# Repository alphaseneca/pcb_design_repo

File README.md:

# pcb_design_repo

A repository for storing and documenting the pcb design files.

### ST-RF

### STM32F4_Breakout

### STM32F4_Breakout_REV2

### STM32WB-Bluetooth_Hardware_Design

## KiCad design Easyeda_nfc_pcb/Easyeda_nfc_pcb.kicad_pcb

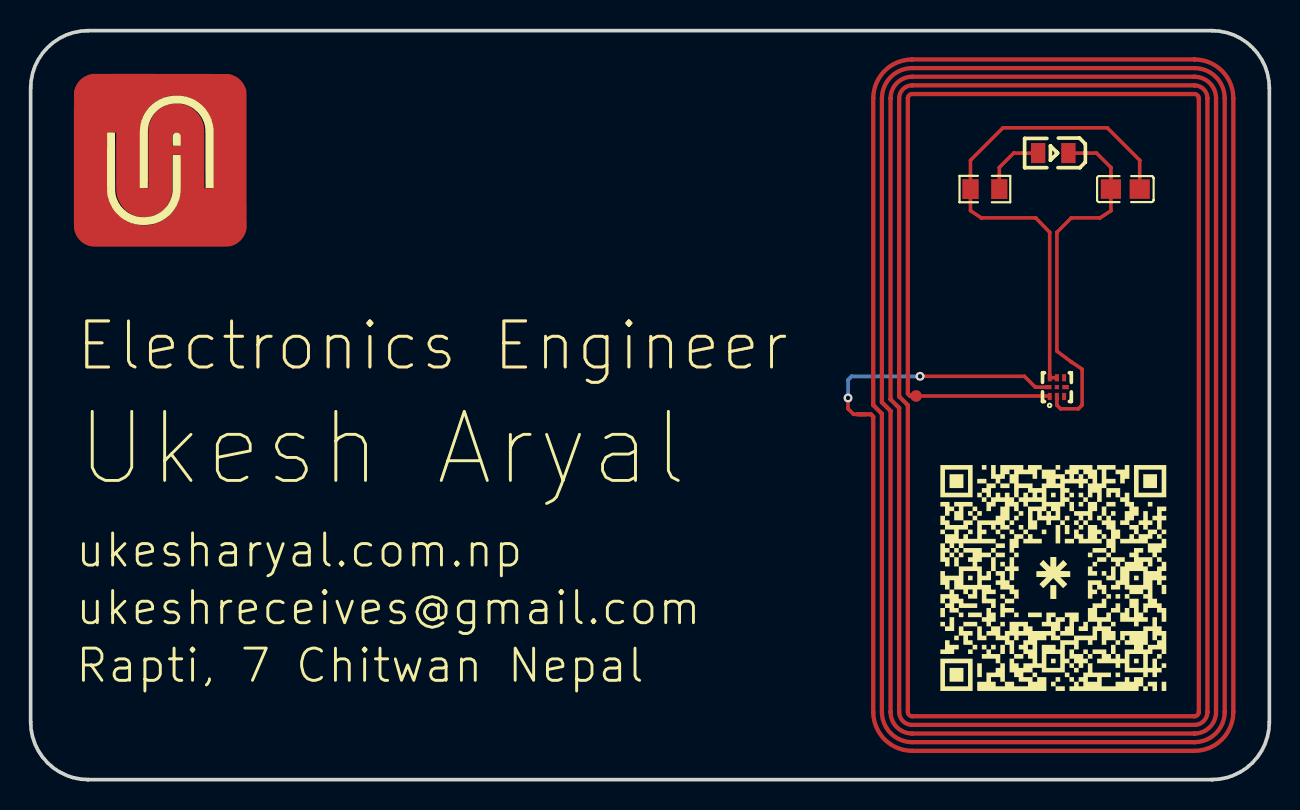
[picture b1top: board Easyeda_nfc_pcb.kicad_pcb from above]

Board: 2 copper layers, 86.0 x 52.0 mm, 5 parts (0 on the bottom side), 5 nets.

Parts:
1: 25X48MM_NFC_ANTENNA
C2: 220nF; C0805
LED1: 17-21SUYC/TR8; LED0805-R-RD
R1: 47Ω; R0805
U1: NT3H2111W0FHKH; XQFN-8_L1.6-W1.6-P0.50-BL

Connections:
LED1_1: LED1.1, R1.1
U1_1: 1.P$2, U1.1
U1_2: C2.1, LED1.2, U1.2
U1_7: C2.2, R1.2, U1.6, U1.7
U1_8: 1.P$1, U1.8

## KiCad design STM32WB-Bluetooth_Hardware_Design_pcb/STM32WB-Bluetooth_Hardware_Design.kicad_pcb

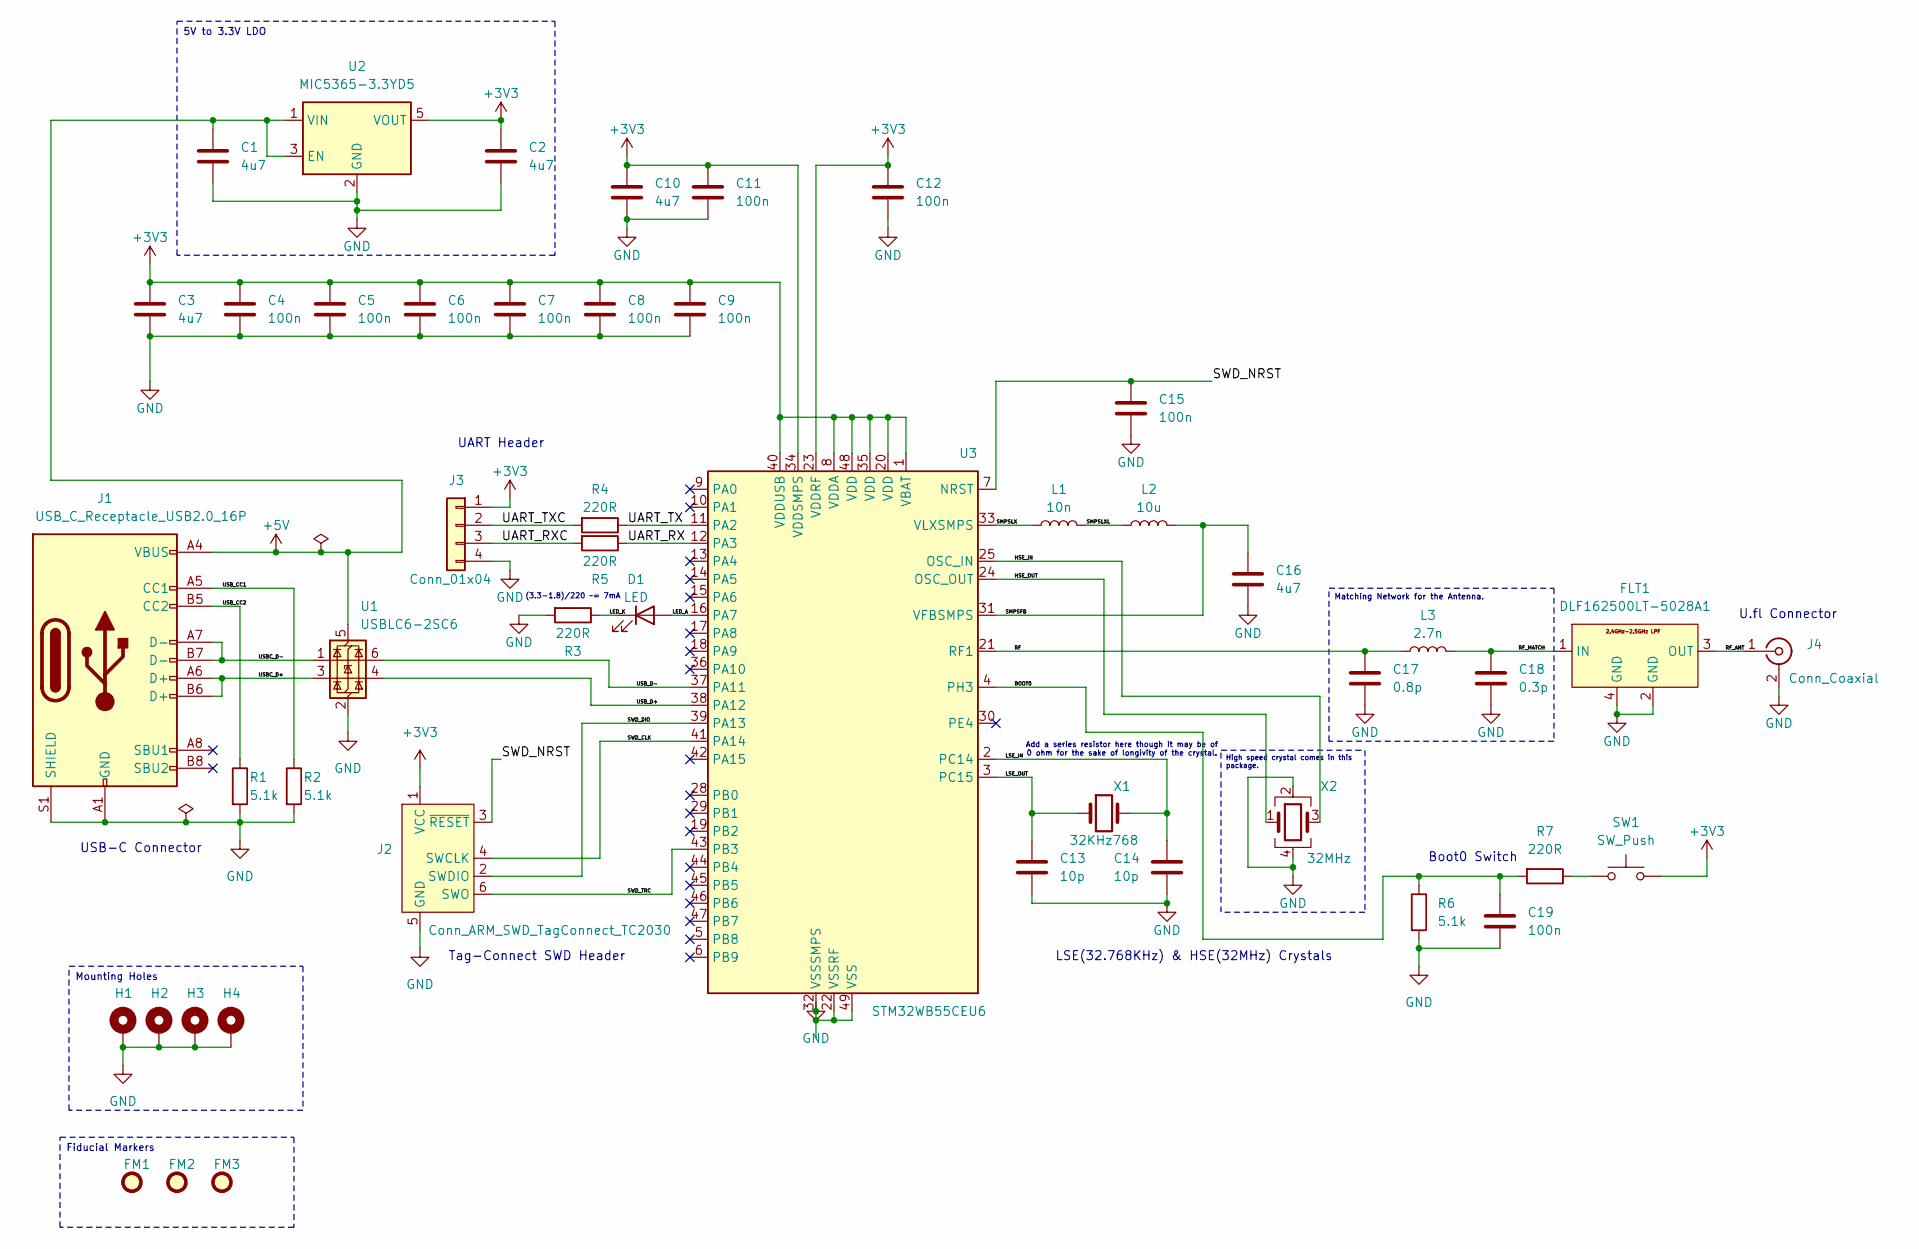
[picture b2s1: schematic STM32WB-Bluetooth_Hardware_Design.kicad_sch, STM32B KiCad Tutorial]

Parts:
C1, C2, C3, C10, C16: 4u7; C_0603_1608Metric
C4, C5, C6, C7, C8, C9, C11, C12, C15, C19: 100n; C_0402_1005Metric
C13, C14: 10p; C_0402_1005Metric
C17: 0.8p; C_0402_1005Metric
C18: 0.3p; C_0402_1005Metric
D1: LED; LED_0402_1005Metric
FLT1: DLF162500LT-5028A1
FM1, FM2, FM3: Fiducial; Fiducial_0.5mm_Mask1mm
H1, H2, H3, H4: MountingHole_Pad; MountingHole_2.2mm_M2_Pad_Via
J1: USB_C_Receptacle_USB2.0_16P; USB_C_Receptacle_GCT_USB4105-xx-A_16P_TopMnt_Horizontal
J2: Conn_ARM_SWD_TagConnect_TC2030; Tag-Connect_TC2030-IDC-FP_2x03_P1.27mm_Vertical
J3: Conn_01x04; Molex_PicoBlade_53048-0410_1x04_P1.25mm_Horizontal
J4: Conn_Coaxial; U.FL_Hirose_U.FL-R-SMT-1_Vertical
L1: 10n; L_0402_1005Metric
L2: 10u; L_0805_2012Metric
L3: 2.7n; L_0402_1005Metric
R1, R2, R6: 5.1k; R_0402_1005Metric
R3, R4, R5, R7: 220R; R_0402_1005Metric
SW1: SW_Push; SW_SPST_B3U-1000P
U1: USBLC6-2SC6; SOT-23-6
U2: MIC5365-3.3YD5; SOT-23-5
U3: STM32WB55CEU6; QFN-48-1EP_7x7mm_P0.5mm_EP5.6x5.6mm
X1: 32KHz768; Crystal_SMD_2012-2Pin_2.0x1.2mm
X2: 32MHz; Crystal_SMD_2016-4Pin_2.0x1.6mm

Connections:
+3V3: C2.1, C3.1, C4.1, C5.1, C6.1, C7.1, C8.1, C9.1, C10.1, C11.1, C12.1, J2.1 (VCC), J3.1, SW1.2, U2.5 (VOUT), U3.1 (VBAT), U3.8 (VDDA), U3.20 (VDD), U3.23 (VDDRF), U3.34 (VDDSMPS), U3.35 (VDD), U3.40 (VDDUSB), U3.48 (VDD)
+5V: C1.1, J1.A4 (VBUS), J1.A9 (VBUS), J1.B4 (VBUS), J1.B9 (VBUS), U1.5 (VBUS), U2.1 (VIN), U2.3 (EN)
/BOOT0: C19.1, R6.1, R7.2, U3.4 (PH3)
/HSE_IN: U3.25 (OSC_IN), X2.3
/HSE_OUT: U3.24 (OSC_OUT), X2.1
/LED_A: D1.2 (A), U3.16 (PA7)
/LED_K: D1.1 (K), R3.1
/LSE_IN: C14.1, U3.2 (PC14), X1.2
/LSE_OUT: C13.1, U3.3 (PC15), X1.1
/RF: C17.1, L3.1, U3.21 (RF1)
/RF_ANT: FLT1.3 (OUT), J4.1 (In)
/RF_MATCH: C18.1, FLT1.1 (IN), L3.2
/SMPSFB: C16.1, L2.2, U3.31 (VFBSMPS)
/SMPSLX: L1.1, U3.33 (VLXSMPS)
/SMPSLXL: L1.2, L2.1
/SWD_CLK: J2.4 (SWCLK), U3.41 (PA14)
/SWD_DIO: J2.2 (SWDIO), U3.39 (PA13)
/SWD_NRST: C15.1, J2.3 (~RESET), U3.7 (NRST)
/SWD_TRC: J2.6 (SWO), U3.43 (PB3)
/UART_RX: R5.1, U3.12 (PA3)
/UART_RXC: J3.3, R5.2
/UART_TX: R4.1, U3.11 (PA2)
/UART_TXC: J3.2, R4.2
/USBC_D+: J1.A6 (D+), J1.B6 (D+), U1.3 (I/O2)
/USBC_D-: J1.A7 (D-), J1.B7 (D-), U1.1 (I/O1)
/USB_CC1: J1.A5 (CC1), R2.1
/USB_CC2: J1.B5 (CC2), R1.1
/USB_D+: U1.4 (I/O2), U3.38 (PA12)
/USB_D-: U1.6 (I/O1), U3.37 (PA11)
GND: C1.2, C2.2, C3.2, C4.2, C5.2, C6.2, C7.2, C8.2, C9.2, C10.2, C11.2, C12.2, C13.2, C14.2, C15.2, C16.2, C17.2, C18.2, C19.2, FLT1.2 (GND), FLT1.4 (GND), H1.1, H2.1, H3.1, H4.1, J1.A1 (GND), J1.A12 (GND), J1.B1 (GND), J1.B12 (GND), J1.S1 (SHIELD), J2.5 (GND), J3.4, J4.2 (Ext), R1.2, R2.2, R3.2, R6.2, U1.2 (GND), U2.2 (GND), U3.22 (VSSRF), U3.32 (VSSSMPS), U3.49 (VSS), X2.2, X2.4
unnamed: R7.1, SW1.1

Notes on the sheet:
Fiducial Markers
Mounting Holes
Matching Network for the Antenna.
5V to 3.3V LDO
High speed crystal comes in this package.
Add a series resistor here though it may be of 0 ohm for the sake of longivity of the crystal.
(3.3-1.8)/220 ~= 7mA
Tag-Connect SWD Header
USB-C Connector
LSE(32.768KHz) & HSE(32MHz) Crystals
U.fl Connector
Boot0 Switch
UART Header

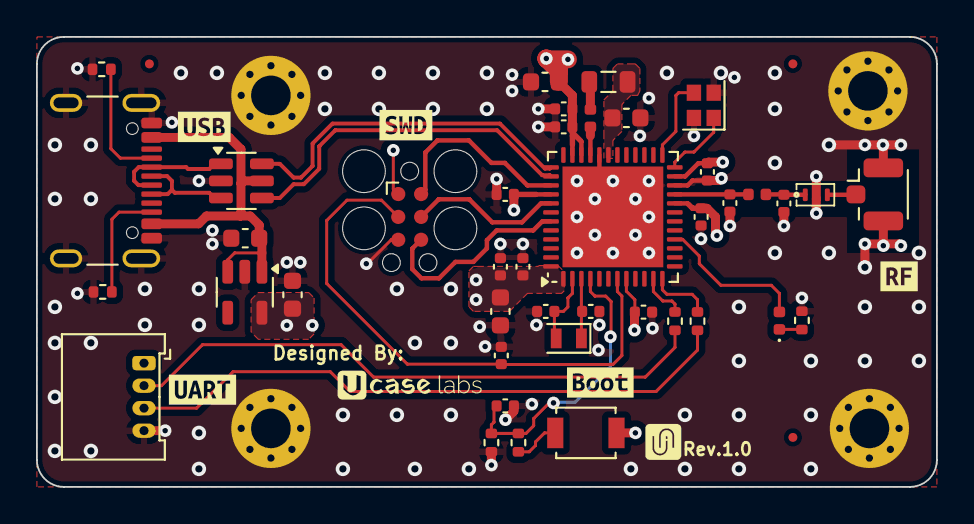
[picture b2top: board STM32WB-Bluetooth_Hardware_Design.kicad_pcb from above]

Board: 4 copper layers, 50.0 x 25.0 mm, 53 parts (0 on the bottom side), 31 nets.

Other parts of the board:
kibuzzard-663E8D7A: G***; kibuzzard-663E8D7A
kibuzzard-663E8D97: G***; kibuzzard-663E8D97
kibuzzard-663E8DAE: G***; kibuzzard-663E8DAE
kibuzzard-663E8DF2: G***; kibuzzard-663E8DF2
kibuzzard-663E8E0C: G***; kibuzzard-663E8E0C

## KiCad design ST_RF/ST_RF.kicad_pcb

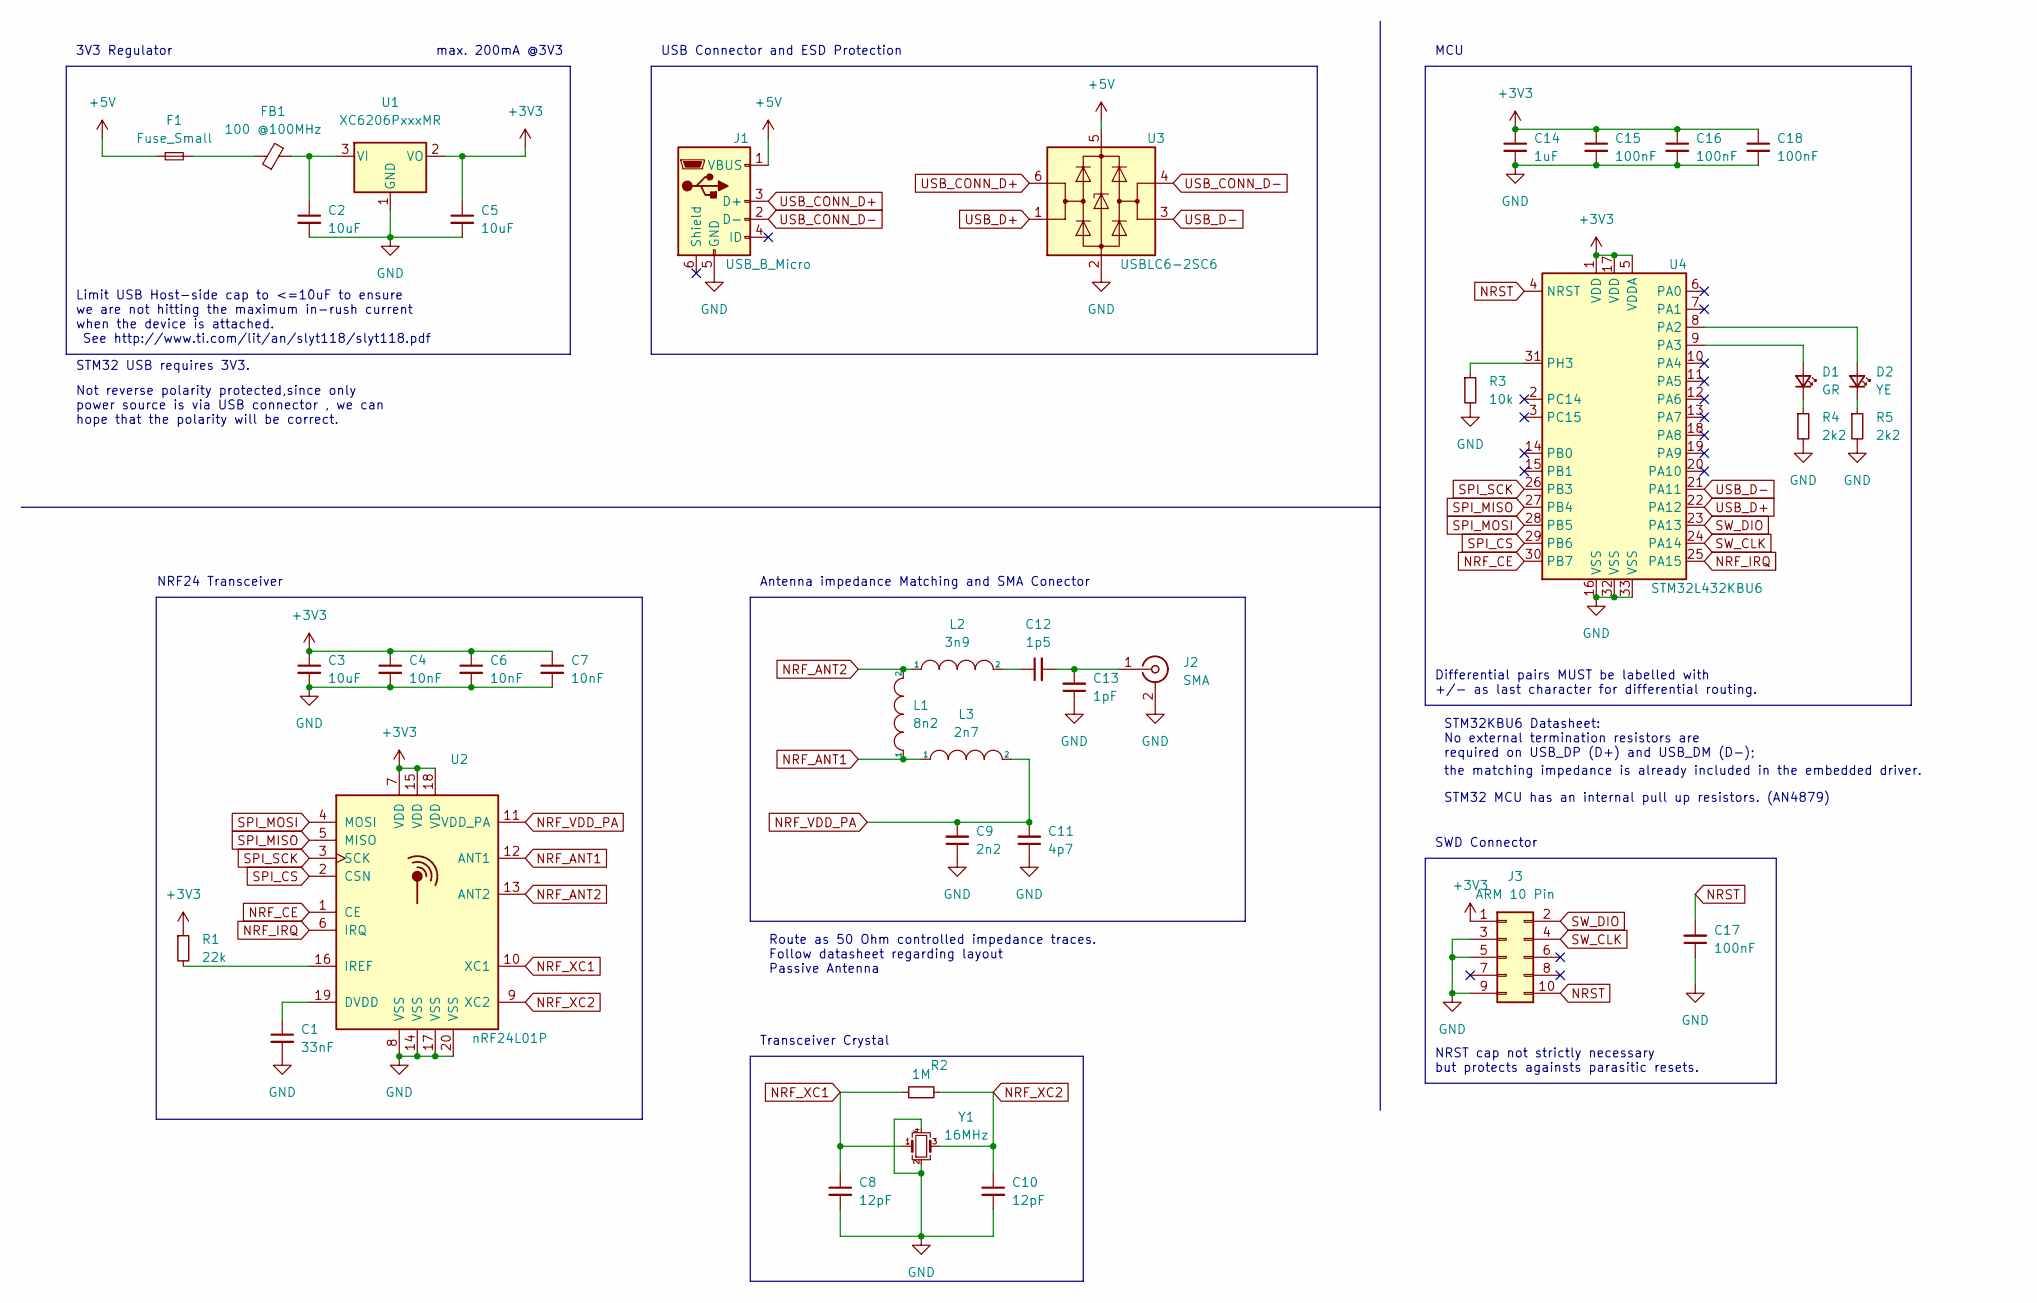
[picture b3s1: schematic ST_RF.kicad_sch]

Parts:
C1: 33nF; C_0402_1005Metric
C2, C3, C5: 10uF; C_0603_1608Metric
C4, C6, C7: 10nF; C_0402_1005Metric
C8, C10: 12pF; C_0402_1005Metric
C9: 2n2; C_0402_1005Metric
C11: 4p7; C_0402_1005Metric
C12: 1p5; C_0402_1005Metric
C13: 1pF; C_0402_1005Metric
C14: 1uF; C_0402_1005Metric
C15, C16, C17, C18: 100nF; C_0402_1005Metric
D1: GR; LED_0603_1608Metric
D2: YE; LED_0603_1608Metric
F1: Fuse_Small; Fuse_1206_3216Metric
FB1: 100 @100MHz; L_0805_2012Metric
J1: USB_B_Micro; USB_Micro-B_Molex-105017-0001
J2: SMA; SMA_Samtec_SMA-J-P-X-ST-EM1_EdgeMount
J3: ARM 10 Pin; PinHeader_2x05_P1.27mm_Vertical
L1: 8n2; L_0402_1005Metric
L2: 3n9; L_0402_1005Metric
L3: 2n7; L_0402_1005Metric
R1: 22k; R_0402_1005Metric
R2: 1M; R_0402_1005Metric
R3: 10k; R_0402_1005Metric
R4, R5: 2k2; R_0603_1608Metric
U1: XC6206PxxxMR; SOT-23
U2: nRF24L01P; QFN-20-1EP_4x4mm_P0.5mm_EP2.5x2.5mm
U3: USBLC6-2SC6; SOT-23-6
U4: STM32L432KBU6; QFN-32-1EP_5x5mm_P0.5mm_EP3.45x3.45mm
Y1: 16MHz; Crystal_SMD_3225-4Pin_3.2x2.5mm

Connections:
+3V3: C3.1, C4.1, C5.1, C6.1, C7.1, C14.1, C15.1, C16.1, C18.1, J3.1, R1.1, U1.2 (VO), U2.7 (VDD), U2.15 (VDD), U2.18 (VDD), U4.1 (VDD), U4.5 (VDDA), U4.17 (VDD)
+5V: F1.1, J1.1 (VBUS), U3.5 (VBUS)
GND: C1.2, C2.2, C3.2, C4.2, C5.2, C6.2, C7.2, C8.2, C9.1, C10.2, C11.1, C13.1, C14.2, C15.2, C16.2, C17.1, C18.2, J1.5 (GND), J2.2 (Ext), J3.3, J3.5, J3.9, R3.2, R4.2, R5.2, U1.1 (GND), U2.8 (VSS), U2.14 (VSS), U2.17 (VSS), U2.20 (VSS), U3.2 (GND), U4.16 (VSS), U4.32 (VSS), U4.33 (VSS), Y1.2, Y1.4
NRF_ANT1: L1.1, L3.1, U2.12 (ANT1)
NRF_ANT2: L1.2, L2.1, U2.13 (ANT2)
NRF_CE: U2.1 (CE), U4.30 (PB7)
NRF_IRQ: U2.6 (IRQ), U4.25 (PA15)
NRF_VDD_PA: C9.2, C11.2, L3.2, U2.11 (VDD_PA)
NRF_XC1: C8.1, R2.1, U2.10 (XC1), Y1.1
NRF_XC2: C10.1, R2.2, U2.9 (XC2), Y1.3
NRST: C17.2, J3.10, U4.4 (NRST)
unnamed: C1.1, U2.19 (DVDD)
unnamed: C2.1, FB1.2, U1.3 (VI)
unnamed: C12.1, L2.2
unnamed: C12.2, C13.2, J2.1 (In)
unnamed: D1.1 (K), R4.1
unnamed: D1.2 (A), U4.9 (PA3)
unnamed: D2.1 (K), R5.1
unnamed: D2.2 (A), U4.8 (PA2)
unnamed: F1.2, FB1.1
unnamed: R1.2, U2.16 (IREF)
unnamed: R3.1, U4.31 (PH3)
SPI_CS: U2.2 (CSN), U4.29 (PB6)
SPI_MISO: U2.5 (MISO), U4.27 (PB4)
SPI_MOSI: U2.4 (MOSI), U4.28 (PB5)
SPI_SCK: U2.3 (SCK), U4.26 (PB3)
SW_CLK: J3.4, U4.24 (PA14)
SW_DIO: J3.2, U4.23 (PA13)
USB_CONN_D+: J1.3 (D+), U3.6 (I/O1)
USB_CONN_D-: J1.2 (D-), U3.4 (I/O2)
USB_D+: U3.1 (I/O1), U4.22 (PA12)
USB_D-: U3.3 (I/O2), U4.21 (PA11)

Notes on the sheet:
Limit USB Host-side cap to <=10uF to ensure we are not hitting the maximum in-rush current when the device is attached. See http://www.ti.com/lit/an/slyt118/slyt118.pdf
Route as 50 Ohm controlled impedance traces. Follow datasheet regarding layout Passive Antenna
max. 200mA @3V3
MCU
Differential pairs MUST be labelled with +/- as last character for differential routing.
the matching impedance is already included in the embedded driver.
STM32KBU6 Datasheet: No external termination resistors are required on USB_DP (D+) and USB_DM (D-);
STM32 USB requires 3V3.
USB Connector and ESD Protection
STM32 MCU has an internal pull up resistors. (AN4879)
Antenna impedance Matching and SMA Conector
Not reverse polarity protected,since only power source is via USB connector , we can hope that the polarity will be correct.
NRF24 Transceiver
Transceiver Crystal
NRST cap not strictly necessary but protects againsts parasitic resets.
SWD Connector
3V3 Regulator

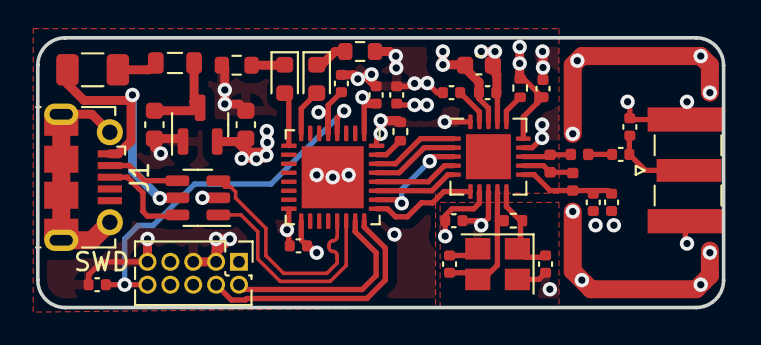
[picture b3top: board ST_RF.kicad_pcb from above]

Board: 4 copper layers, 38.1 x 15.0 mm, 38 parts (0 on the bottom side), 32 nets.

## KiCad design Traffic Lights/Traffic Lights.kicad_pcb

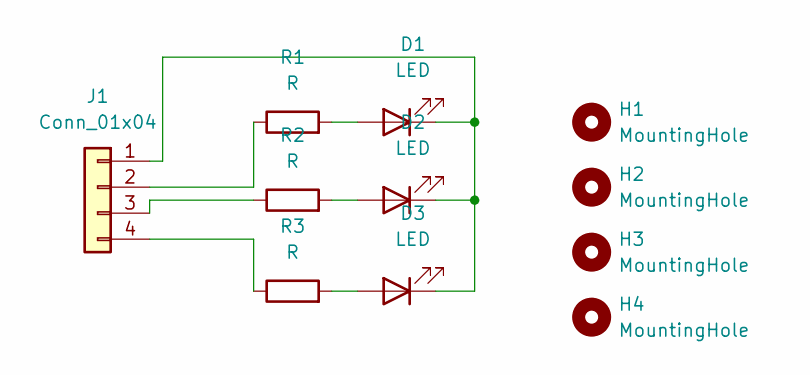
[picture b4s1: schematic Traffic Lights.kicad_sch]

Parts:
D1, D2, D3: LED; LED_D3.0mm
H1, H2, H3, H4: MountingHole; MountingHole_2.5mm_Pad
J1: Conn_01x04; PinHeader_1x04_P2.54mm_Horizontal
R1, R2, R3: R; R_Axial_DIN0204_L3.6mm_D1.6mm_P5.08mm_Horizontal

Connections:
unnamed: D1.1 (K), D2.1 (K), D3.1 (K), J1.1
unnamed: D1.2 (A), R1.2
unnamed: D2.2 (A), R2.2
unnamed: D3.2 (A), R3.2
unnamed: J1.2, R1.1
unnamed: J1.3, R2.1
unnamed: J1.4, R3.1

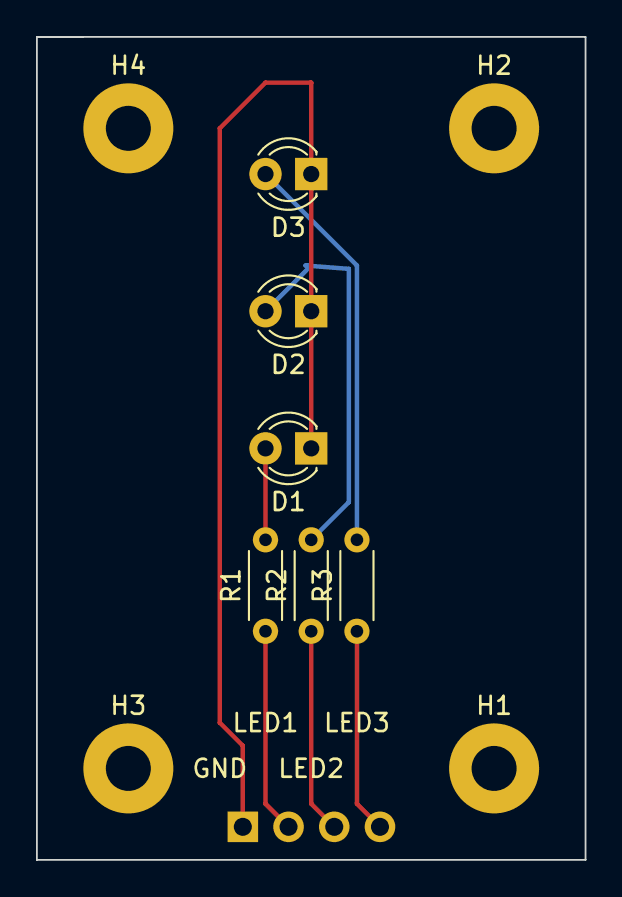
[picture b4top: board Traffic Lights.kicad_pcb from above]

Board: 2 copper layers, 30.5 x 45.7 mm, 11 parts (1 on the bottom side), 7 nets.

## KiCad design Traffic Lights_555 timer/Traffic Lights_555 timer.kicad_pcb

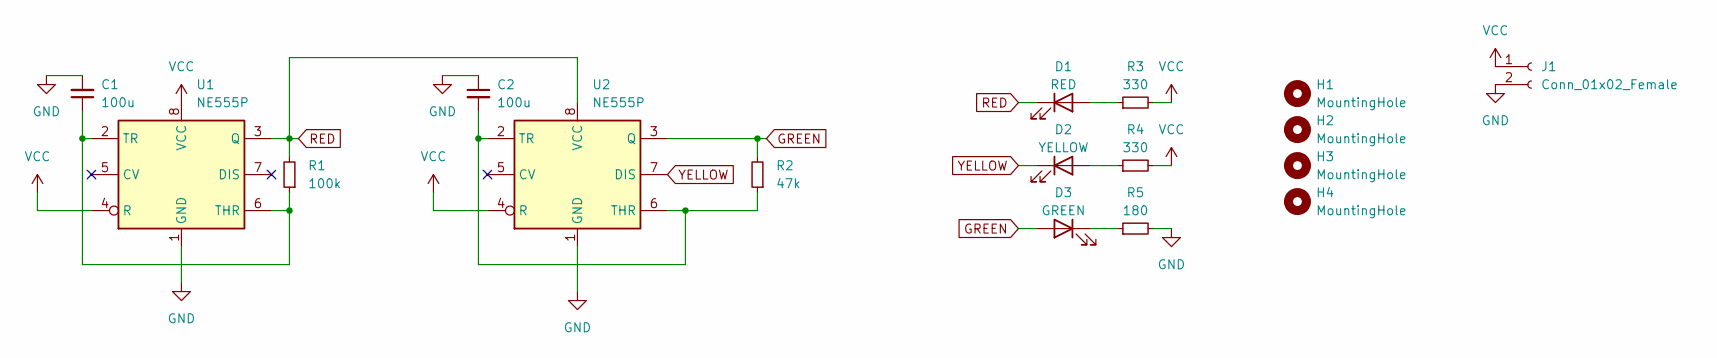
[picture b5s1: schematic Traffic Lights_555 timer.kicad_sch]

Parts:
C1, C2: 100u; C_0402_1005Metric_Pad0.74x0.62mm_HandSolder
D1: RED; LED_0603_1608Metric_Pad1.05x0.95mm_HandSolder
D2: YELLOW; LED_0603_1608Metric_Pad1.05x0.95mm_HandSolder
D3: GREEN; LED_0603_1608Metric_Pad1.05x0.95mm_HandSolder
H1, H2, H3, H4: MountingHole; MountingHole_3.2mm_M3
J1: Conn_01x02_Female; PinHeader_1x02_P2.00mm_Vertical_SMD_Pin1Right
R1: 100k; R_0402_1005Metric_Pad0.72x0.64mm_HandSolder
R2: 47k; R_0402_1005Metric_Pad0.72x0.64mm_HandSolder
R3, R4: 330; R_0603_1608Metric_Pad0.98x0.95mm_HandSolder
R5: 180; R_0603_1608Metric_Pad0.98x0.95mm_HandSolder
U1, U2: NE555P; DIP-8_W7.62mm

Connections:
GND: C1.2, C2.1, J1.2, R5.2, U1.1 (GND), U2.1 (GND)
GREEN: D3.2 (A), R2.2, U2.3 (Q)
unnamed: C1.1, R1.1, U1.2 (TR), U1.6 (THR)
unnamed: C2.2, R2.1, U2.2 (TR), U2.6 (THR)
unnamed: D1.2 (A), R3.1
unnamed: D2.2 (A), R4.1
unnamed: D3.1 (K), R5.1
RED: D1.1 (K), R1.2, U1.3 (Q), U2.8 (VCC)
VCC: J1.1, R3.2, R4.2, U1.4 (R), U1.8 (VCC), U2.4 (R)
YELLOW: D2.1 (K), U2.7 (DIS)

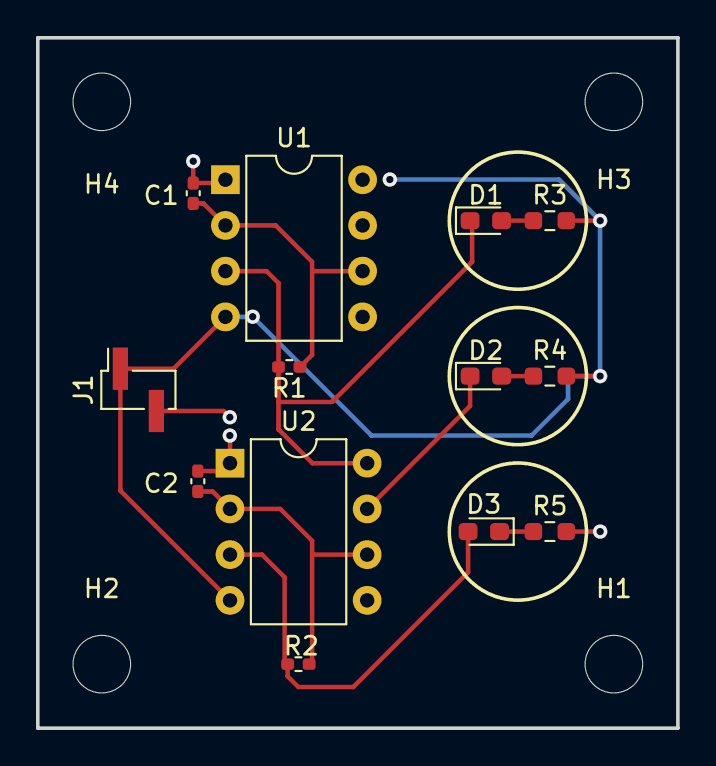
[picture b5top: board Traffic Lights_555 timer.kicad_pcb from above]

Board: 2 copper layers, 35.6 x 38.4 mm, 17 parts (0 on the bottom side), 10 nets.

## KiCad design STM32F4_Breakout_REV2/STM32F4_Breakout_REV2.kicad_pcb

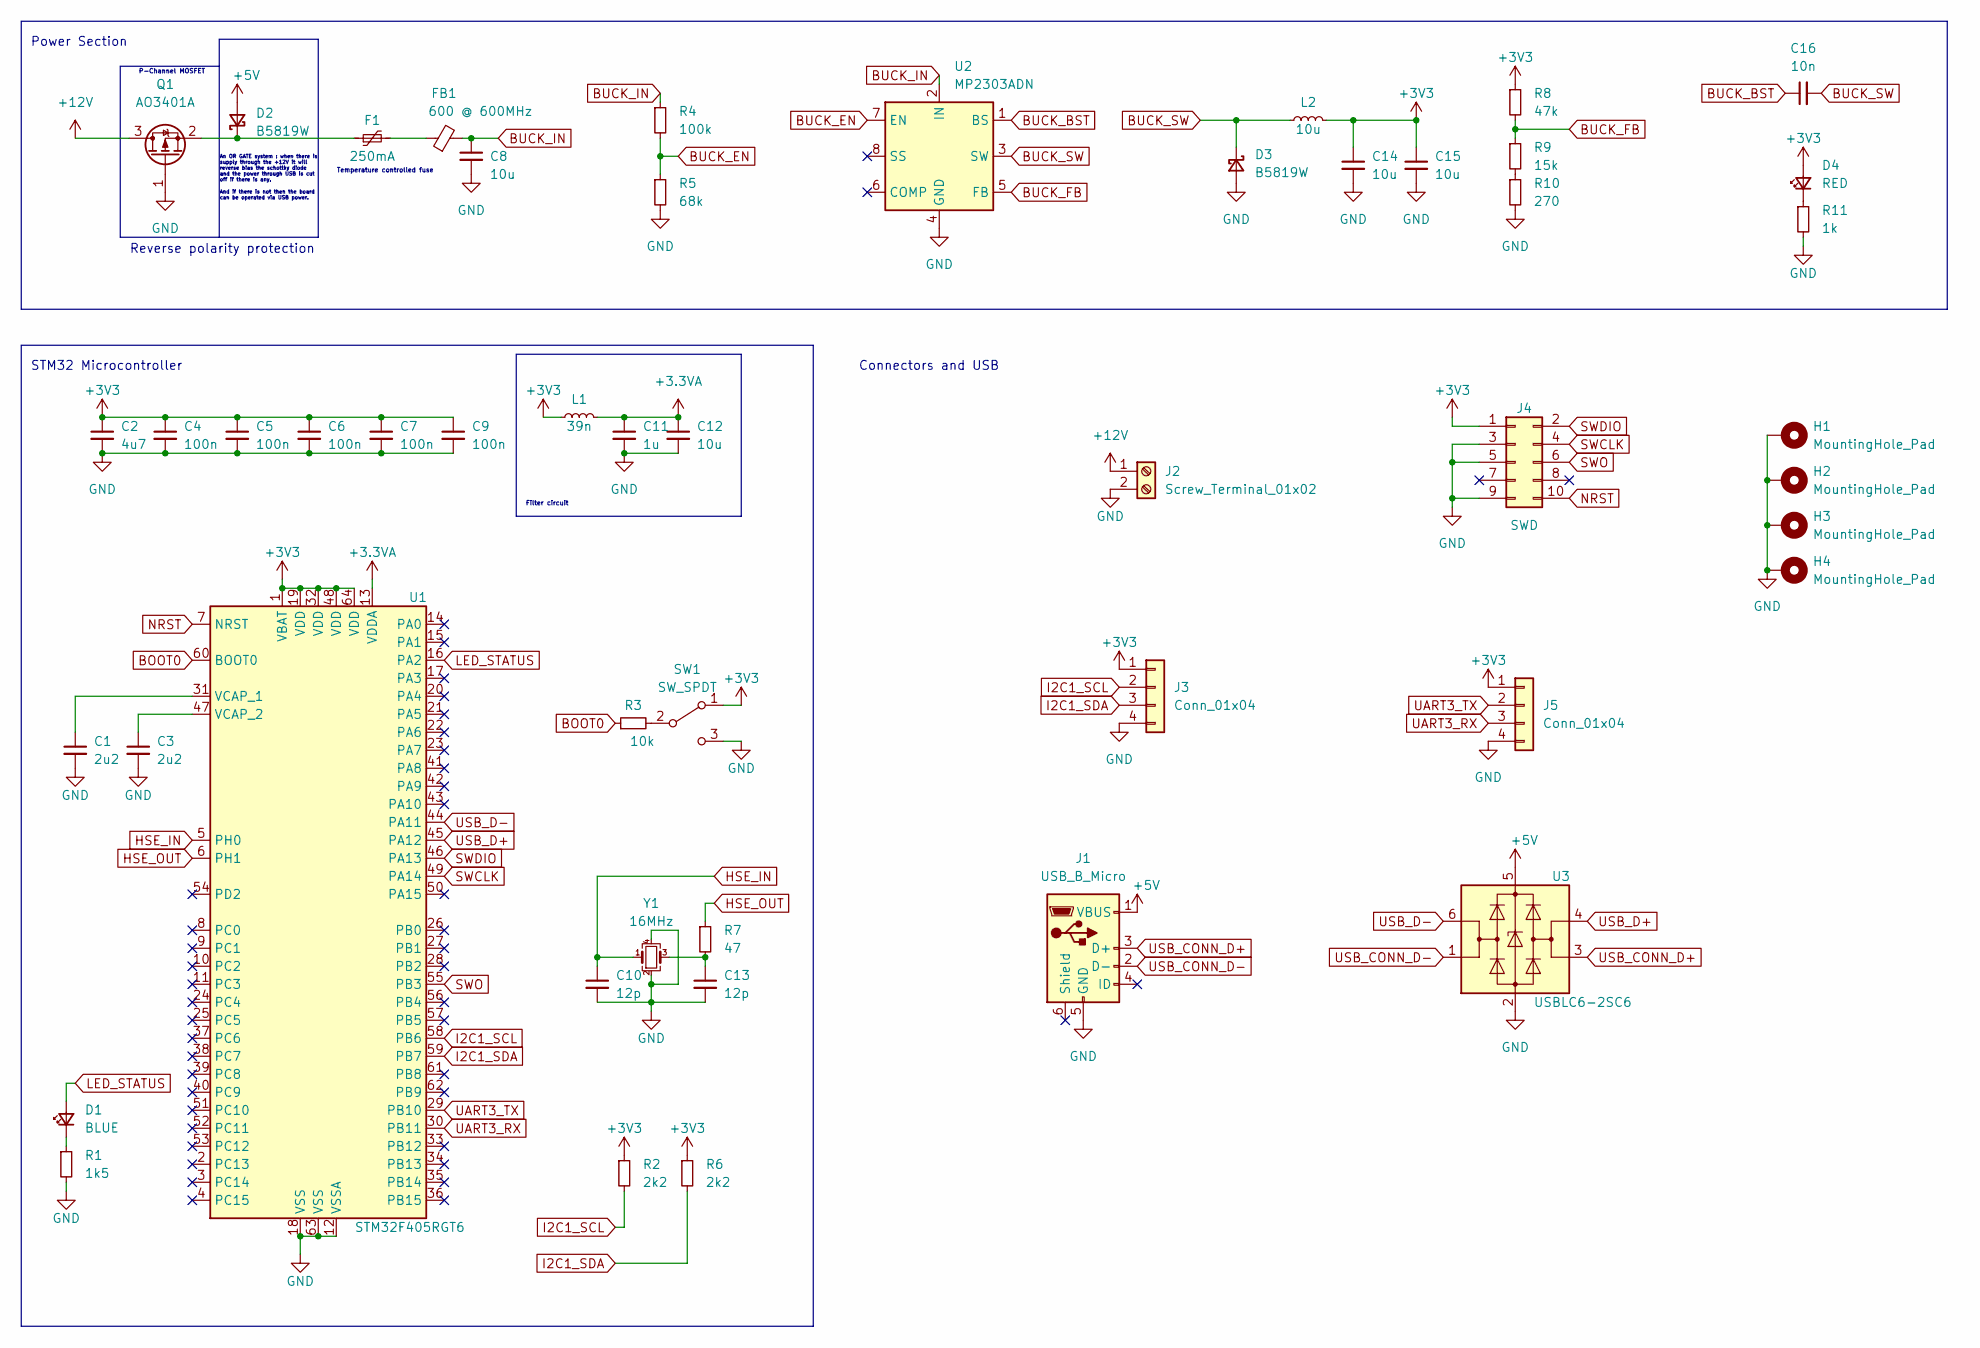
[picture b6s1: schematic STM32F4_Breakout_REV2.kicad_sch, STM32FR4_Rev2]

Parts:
C1, C3: 2u2; C_0603_1608Metric
C2: 4u7; C_0603_1608Metric
C4, C5, C6, C7, C9: 100n; C_0402_1005Metric
C8: 10u; C_0603_1608Metric
C10, C13: 12p; C_0402_1005Metric
C11: 1u; C_0402_1005Metric
C12: 10u; C_0402_1005Metric
C14, C15: 10u; C_1206_3216Metric
C16: 10n; C_0603_1608Metric
D1: BLUE; LED_0603_1608Metric
D2, D3: B5819W; D_SOD-123
D4: RED; LED_0603_1608Metric
F1: 250mA; Fuse_1206_3216Metric
FB1: 600 @ 600MHz; L_0805_2012Metric
H1, H2, H3, H4: MountingHole_Pad; MountingHole_4.3mm_M4_Pad_Via
J1: USB_B_Micro; USB_Micro-B_Amphenol_10118193-0002LF_Horizontal
J2: Screw_Terminal_01x02; TerminalBlock_Phoenix_PT-1,5-2-3.5-H_1x02_P3.50mm_Horizontal
J3, J5: Conn_01x04; Molex_PicoBlade_53048-0410_1x04_P1.25mm_Horizontal
J4: SWD; PinHeader_2x05_P1.27mm_Vertical_SMD
L1: 39n; L_0402_1005Metric
L2: 10u; L_Sunlord_MWSA0518S
Q1: AO3401A; SOT-23
R1: 1k5; R_0603_1608Metric
R2, R6: 2k2; R_0402_1005Metric
R3: 10k; R_0402_1005Metric
R4: 100k; R_0603_1608Metric
R5: 68k; R_0603_1608Metric
R7: 47; R_0402_1005Metric
R8: 47k; R_0603_1608Metric
R9: 15k; R_0603_1608Metric
R10: 270; R_0603_1608Metric
R11: 1k; R_0603_1608Metric
SW1: SW_SPDT; SW_SPDT_PCM12
U1: STM32F405RGT6; LQFP-64_10x10mm_P0.5mm
U2: MP2303ADN; SOIC-8-1EP_3.9x4.9mm_P1.27mm_EP2.62x3.51mm
U3: USBLC6-2SC6; SOT-23-6
Y1: 16MHz; Crystal_SMD_3225-4Pin_3.2x2.5mm

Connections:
+3.3VA: C11.1, C12.1, L1.2, U1.13 (VDDA)
+3V3: C2.1, C4.1, C5.1, C6.1, C7.1, C9.1, C14.1, C15.1, D4.2 (A), J3.1, J4.1, J5.1, L1.1, L2.2, R2.1, R6.1, R8.1, SW1.1 (A), U1.1 (VBAT), U1.19 (VDD), U1.32 (VDD), U1.48 (VDD), U1.64 (VDD)
+5V: D2.2 (A), J1.1 (VBUS), U3.5 (VBUS)
+12V: J2.1, Q1.3 (D)
BOOT0: R3.1, U1.60 (BOOT0)
BUCK_BST: C16.1, U2.1 (BS)
BUCK_EN: R4.2, R5.1, U2.7 (EN)
BUCK_FB: R8.2, R9.1, U2.5 (FB)
BUCK_IN: C8.1, FB1.2, R4.1, U2.2 (IN)
BUCK_SW: C16.2, D3.1 (K), L2.1, U2.3 (SW)
GND: C1.2, C2.2, C3.2, C4.2, C5.2, C6.2, C7.2, C8.2, C9.2, C10.2, C11.2, C12.2, C13.2, C14.2, C15.2, D3.2 (A), H1.1, H2.1, H3.1, H4.1, J1.5 (GND), J2.2, J3.4, J4.3, J4.5, J4.9, J5.4, Q1.1 (G), R1.2, R5.2, R10.2, R11.2, SW1.3 (C), U1.12 (VSSA), U1.18 (VSS), U1.63 (VSS), U2.4 (GND), U3.2 (GND), Y1.2, Y1.4
HSE_IN: C10.1, U1.5 (PH0), Y1.1
HSE_OUT: R7.1, U1.6 (PH1)
I2C1_SCL: J3.2, R2.2, U1.58 (PB6)
I2C1_SDA: J3.3, R6.2, U1.59 (PB7)
LED_STATUS: D1.2 (A), U1.16 (PA2)
NRST: J4.10, U1.7 (NRST)
unnamed: C13.1, R7.2, Y1.3
unnamed: D1.1 (K), R1.1
unnamed: D2.1 (K), F1.1, Q1.2 (S)
unnamed: D4.1 (K), R11.1
unnamed: F1.2, FB1.1
unnamed: R9.2, R10.1
unnamed: R3.2, SW1.2 (B)
unnamed: C1.1, U1.31 (VCAP_1)
unnamed: C3.1, U1.47 (VCAP_2)
SWCLK: J4.4, U1.49 (PA14)
SWDIO: J4.2, U1.46 (PA13)
SWO: J4.6, U1.55 (PB3)
UART3_RX: J5.3, U1.30 (PB11)
UART3_TX: J5.2, U1.29 (PB10)
USB_CONN_D+: J1.3 (D+), U3.3 (I/O2)
USB_CONN_D-: J1.2 (D-), U3.1 (I/O1)
USB_D+: U1.45 (PA12), U3.4 (I/O2)
USB_D-: U1.44 (PA11), U3.6 (I/O1)

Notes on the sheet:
Temperature controlled fuse
And if there is not then the board can be operated via USB power.
STM32 Microcontroller
Filter circuit
Connectors and USB
Reverse polarity protection
P-Channel MOSFET
Power Section
An OR GATE system : when there is supply through the +12V it will reverse bias the schottky diode and the power through USB is cut off if there is any.

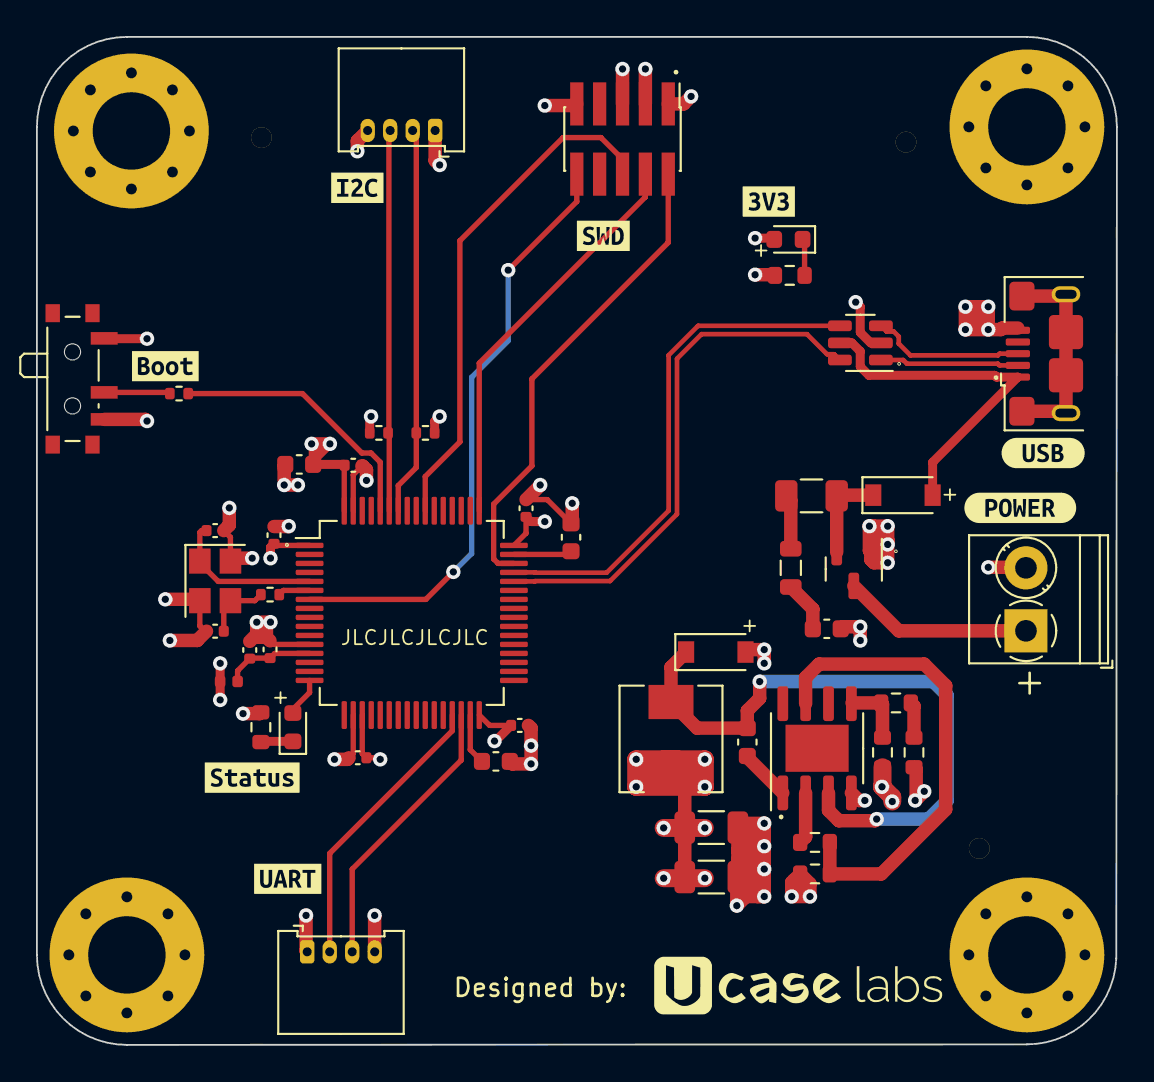
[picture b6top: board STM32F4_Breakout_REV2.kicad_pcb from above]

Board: 4 copper layers, 60.0 x 56.0 mm, 59 parts (1 on the bottom side), 35 nets.

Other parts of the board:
kibuzzard-6631EB7E: G***; kibuzzard-6631EB7E
kibuzzard-6631EB89: G***; kibuzzard-6631EB89
kibuzzard-6631EB97: G***; kibuzzard-6631EB97
kibuzzard-6631EBD3: G***; kibuzzard-6631EBD3
kibuzzard-6631EC82: G***; kibuzzard-6631EC82
kibuzzard-6631ED4F: G***; kibuzzard-6631ED4F
kibuzzard-6631ED5C: G***; kibuzzard-6631ED5C
kibuzzard-6631ED24: G***; kibuzzard-6631ED24
kibuzzard-6631F910: G***; kibuzzard-6631F910

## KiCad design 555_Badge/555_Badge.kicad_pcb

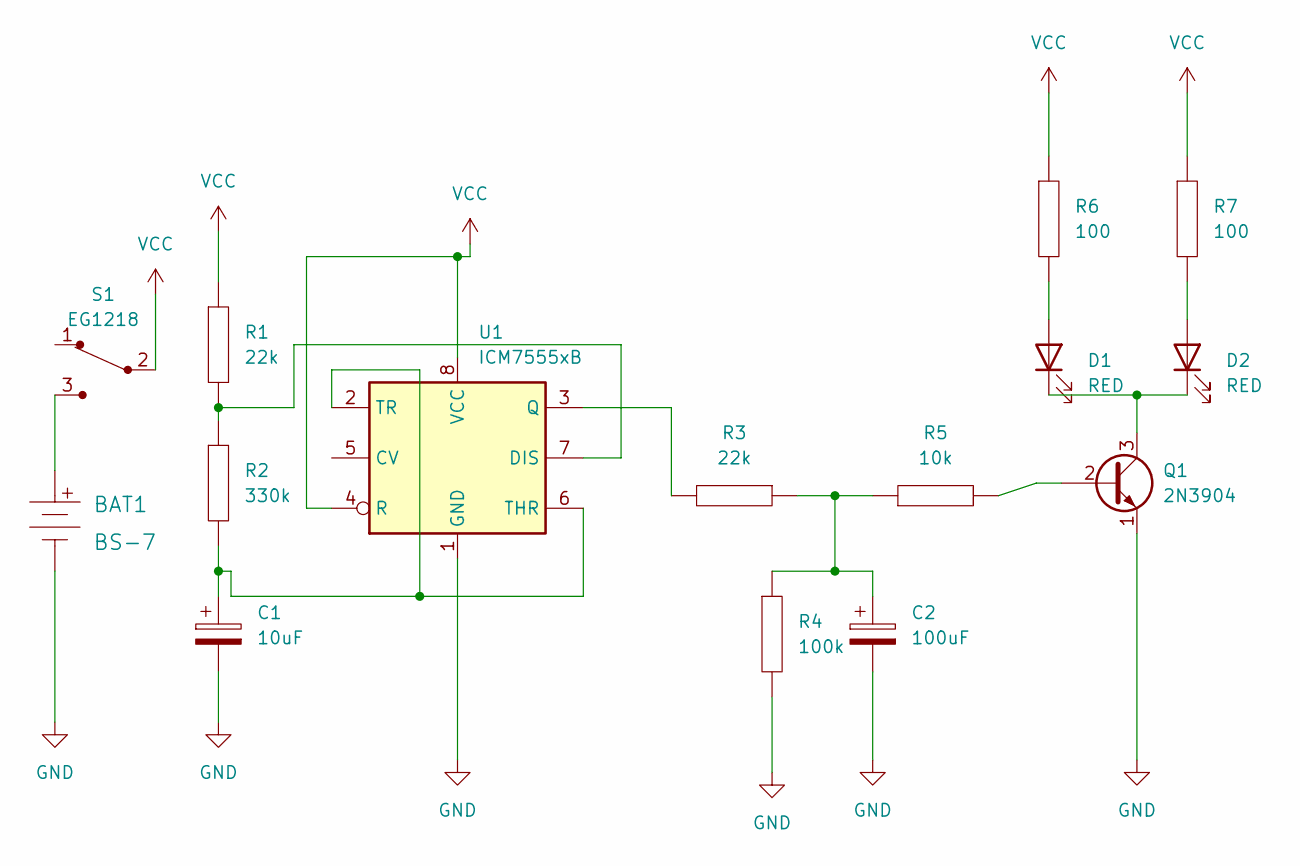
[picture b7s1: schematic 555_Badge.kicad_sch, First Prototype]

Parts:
BAT1: BS-7; Battery_Holder_Coin_2032_BS-7; MPN BS-7; Digi-Key_PN BS-7-ND
C1: 10uF; CP_Radial_D5.0mm_P2.00mm
C2: 100uF; CP_Radial_D6.3mm_P2.50mm
D1, D2: RED; LED_D3.0mm
Q1: 2N3904; TO-92_Inline
R1, R3: 22k; R_Axial_DIN0207_L6.3mm_D2.5mm_P7.62mm_Horizontal
R2: 330k; R_Axial_DIN0207_L6.3mm_D2.5mm_P7.62mm_Horizontal
R4: 100k; R_Axial_DIN0207_L6.3mm_D2.5mm_P7.62mm_Horizontal
R5: 10k; R_Axial_DIN0207_L6.3mm_D2.5mm_P7.62mm_Horizontal
R6, R7: 100; R_Axial_DIN0207_L6.3mm_D2.5mm_P7.62mm_Horizontal
S1: EG1218; Switch_Slide_11.6x4mm_EG1218; MPN EG1218; Digi-Key_PN EG1903-ND
U1: ICM7555xB; SOIC-8_3.9x4.9mm_P1.27mm

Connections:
GND: BAT1.Neg, C1.2, C2.2, Q1.1 (E), R4.2, U1.1 (GND)
unnamed: BAT1.Pos, S1.3
unnamed: C1.1, R2.2, U1.2 (TR), U1.6 (THR)
unnamed: C2.1, R3.1, R4.1, R5.1
unnamed: D1.1 (K), D2.1 (K), Q1.3 (C)
unnamed: D1.2 (A), R6.2
unnamed: D2.2 (A), R7.2
unnamed: Q1.2 (B), R5.2
unnamed: R1.2, R2.1, U1.7 (DIS)
unnamed: R3.2, U1.3 (Q)
VCC: R1.1, R6.1, R7.1, S1.2, U1.4 (R), U1.8 (VCC)
